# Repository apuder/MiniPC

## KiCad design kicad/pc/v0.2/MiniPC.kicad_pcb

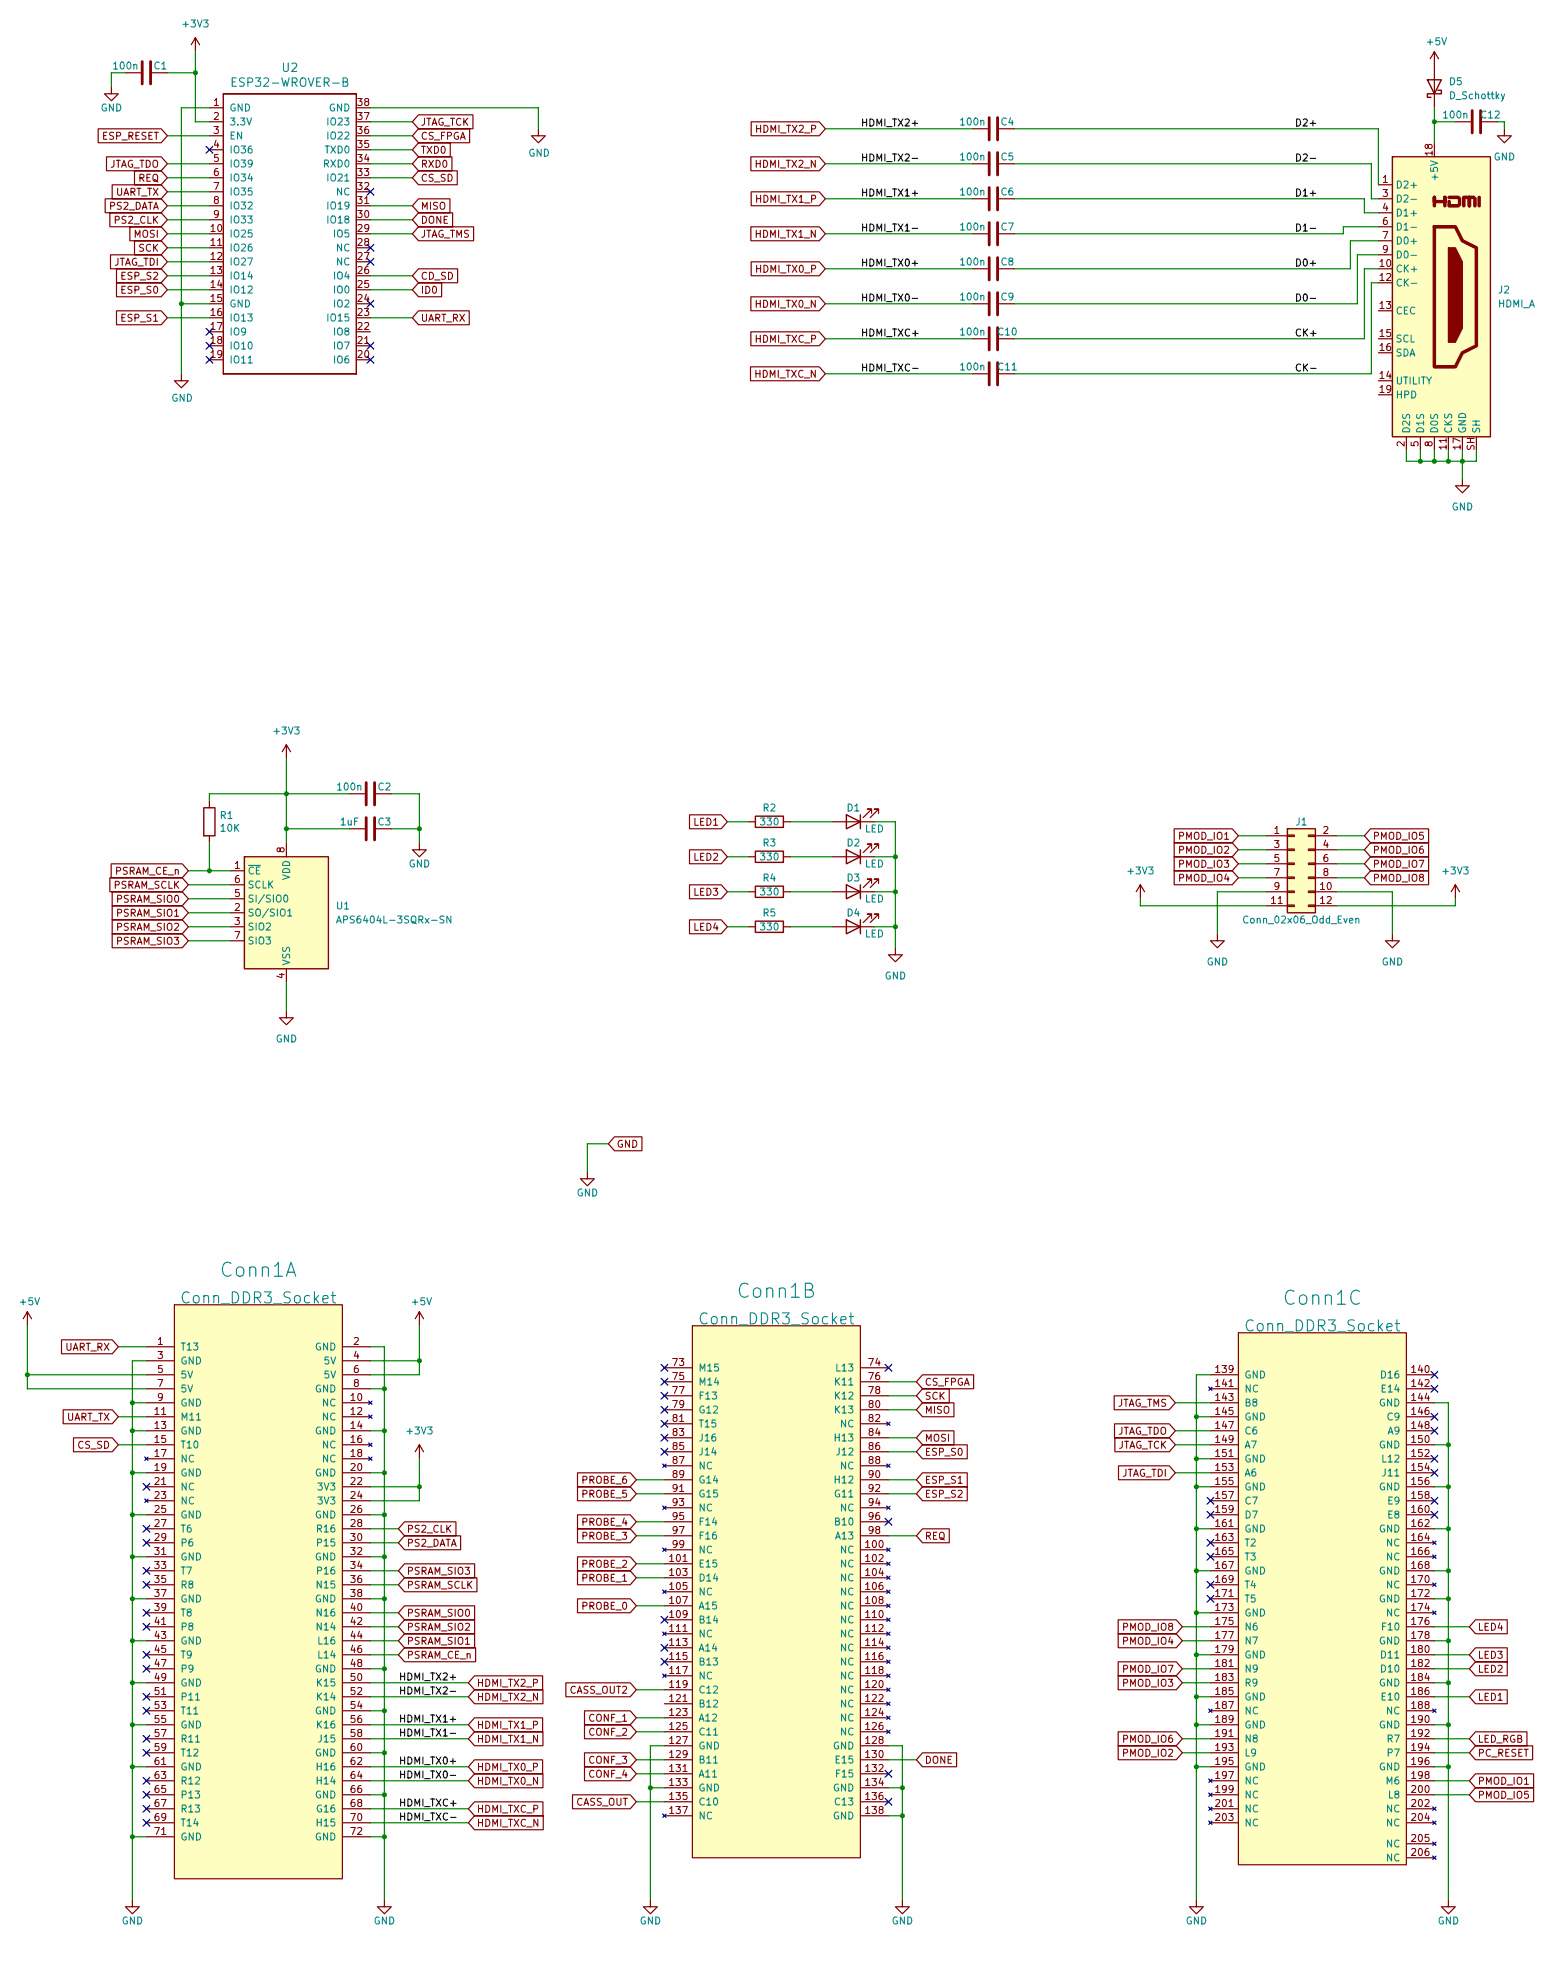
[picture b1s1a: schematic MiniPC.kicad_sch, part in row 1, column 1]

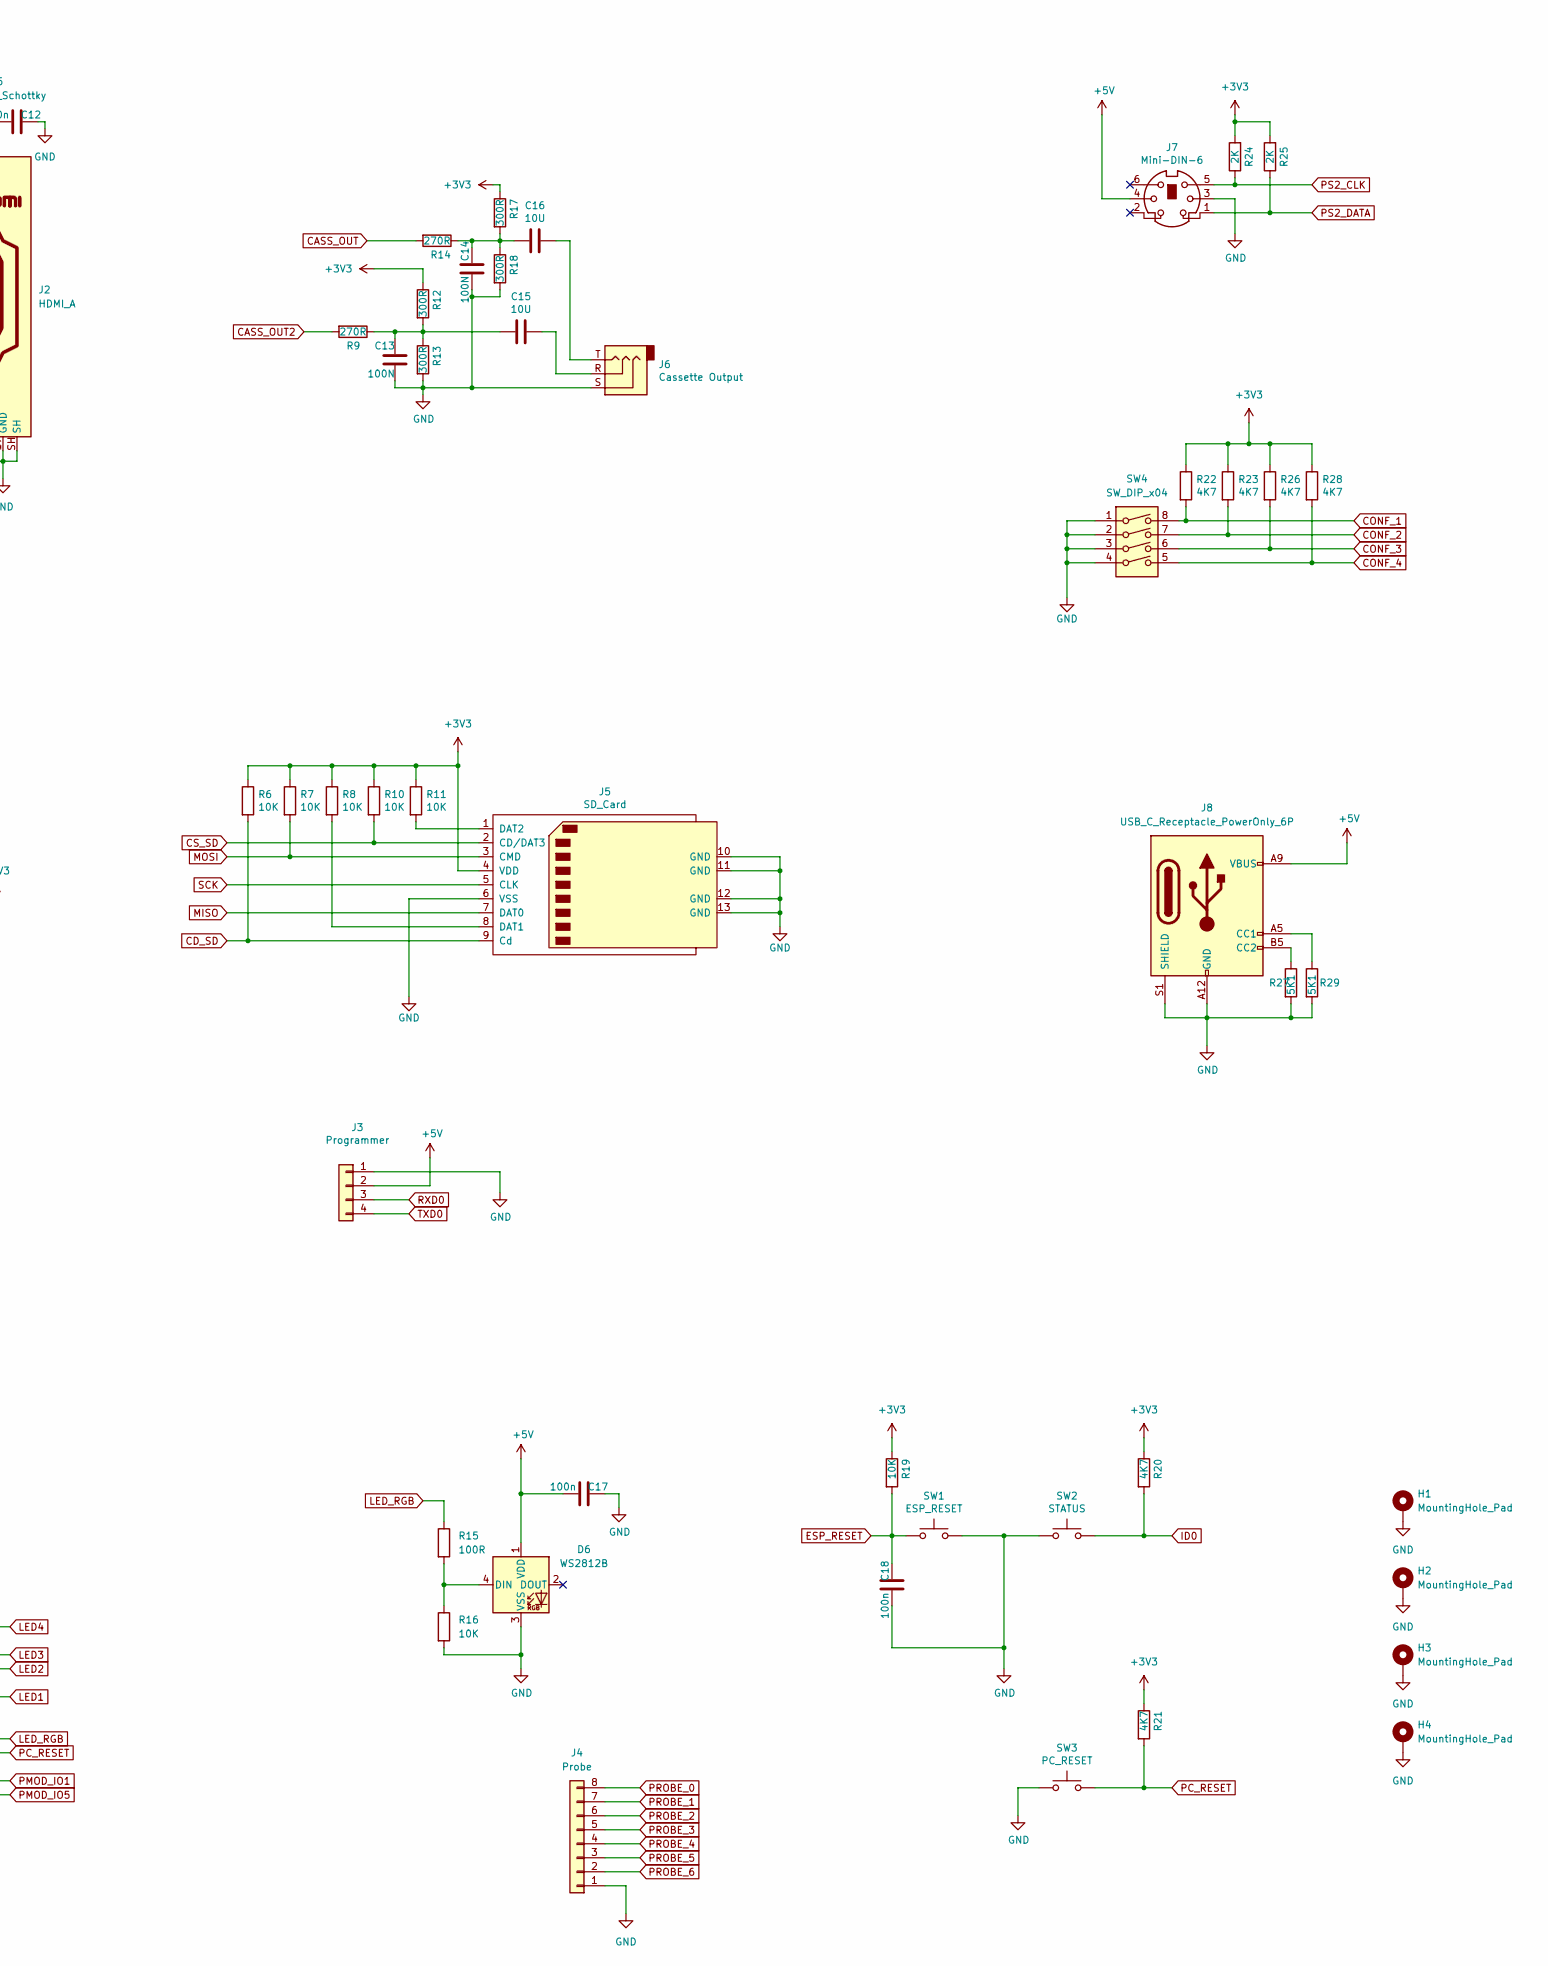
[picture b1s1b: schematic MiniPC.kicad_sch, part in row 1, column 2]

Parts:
C1, C2, C4, C5, C6, C7, C8, C9, C10, C11, C12, C17, C18: 100n; C_0805_2012Metric_Pad1.18x1.45mm_HandSolder
C3: 1uF; C_0805_2012Metric_Pad1.18x1.45mm_HandSolder
C13, C14: 100N; C_0805_2012Metric_Pad1.18x1.45mm_HandSolder
C15, C16: 10U; C_1206_3216Metric_Pad1.33x1.80mm_HandSolder
Conn1: Conn_DDR3_Socket; DDR3_socket; LCSC C306045
D1: LED; LED_0805_2012Metric_Pad1.15x1.40mm_HandSolder; LCSC C84256
D2, D3, D4: LED; LED_0805_2012Metric_Pad1.15x1.40mm_HandSolder
D5: D_Schottky; D_SOD-323; LCSC C1884554
D6: WS2812B; LED_WS2812B_PLCC4_5.0x5.0mm_P3.2mm; LCSC C2761795
H1, H2, H3, H4: MountingHole_Pad; MountingHole_3mm_Pad_Via
J1: Conn_02x06_Odd_Even; PinSocket_2x06_P2.54mm_Vertical; LCSC C358728
J2: HDMI_A; HDMI_A_Molex_208658-1001_Horizontal; LCSC C5184845
J3: Programmer; PinHeader_1x04_P2.54mm_Vertical; LCSC C2691448
J4: Probe; PinHeader_1x08_P2.54mm_Vertical
J5: SD_Card; TFP09-2-12B; LCSC C91145
J6: Cassette Output; Jack_3.5mm_CUI_SJ1-3535NG_Horizontal_CircularHoles; LCSC C2884945
J7: Mini-DIN-6; minidin_6_ps2_pcb_mount; LCSC C77848
J8: USB_C_Receptacle_PowerOnly_6P; USB_C_Receptacle_GCT_USB4125-xx-x_6P_TopMnt_Horizontal; LCSC C168701
R1, R6, R7, R8, R10, R11, R16, R19: 10K; R_0805_2012Metric_Pad1.20x1.40mm_HandSolder
R2, R3, R4, R5: 330; R_0805_2012Metric_Pad1.20x1.40mm_HandSolder
R9, R14: 270R; R_0805_2012Metric_Pad1.20x1.40mm_HandSolder
R12, R13, R17, R18: 300R; R_0805_2012Metric_Pad1.20x1.40mm_HandSolder
R15: 100R; R_0805_2012Metric_Pad1.20x1.40mm_HandSolder
R20, R21, R22, R23, R26, R28: 4K7; R_0805_2012Metric_Pad1.20x1.40mm_HandSolder
R24, R25: 2K; R_0805_2012Metric_Pad1.20x1.40mm_HandSolder
R27, R29: 5K1; R_0805_2012Metric_Pad1.20x1.40mm_HandSolder
SW1: ESP_RESET; SW_Push_1P1T_NO_E-Switch_TL3301NxxxxxG; LCSC C255812
SW2: STATUS; SW_Push_1P1T_NO_E-Switch_TL3301NxxxxxG; LCSC C255812
SW3: PC_RESET; SW_Push_1P1T_NO_E-Switch_TL3301NxxxxxG; LCSC C255812
SW4: SW_DIP_x04; SW_DIP_SPSTx04_Slide_6.7x11.72mm_W8.61mm_P2.54mm_LowProfile; LCSC C2842911
U1: APS6404L-3SQRx-SN; SOIC-8_3.9x4.9mm_P1.27mm; LCSC C5333729
U2: ESP32-WROVER-B; ESP32-WROVER; LCSC C529589

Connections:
+3V3: C1.2, C2.1, C3.1, Conn1.22 (3V3), Conn1.24 (3V3), J1.11, J1.12, J5.4 (VDD), R1.1, R6.1, R7.1, R8.1, R10.1, R11.1, R12.1, R17.1, R19.1, R20.1, R21.1, R22.1, R23.1, R24.2, R25.2, R26.1, R28.1, U1.8 (VDD), U2.2 (3.3V)
+5V: C17.1, Conn1.4 (5V), Conn1.5 (5V), Conn1.6 (5V), Conn1.7 (5V), D5.2 (A), D6.1 (VDD), J3.2, J7.4, J8.A9 (VBUS), J8.B9 (VBUS)
/CK+: C10.2, J2.10 (CK+)
/CK-: C11.2, J2.12 (CK-)
/D0+: C8.2, J2.7 (D0+)
/D0-: C9.2, J2.9 (D0-)
/D1+: C6.2, J2.4 (D1+)
/D1-: C7.2, J2.6 (D1-)
/D2+: C4.2, J2.1 (D2+)
/D2-: C5.2, J2.3 (D2-)
CASS_OUT: Conn1.135 (C10), R14.2
CASS_OUT2: Conn1.119 (C12), R9.2
CD_SD: J5.9 (Cd), R6.2, U2.26 (IO4)
CONF_1: Conn1.123 (A12), R22.2, SW4.8
CONF_2: Conn1.125 (C11), R23.2, SW4.7
CONF_3: Conn1.129 (B11), R26.2, SW4.6
CONF_4: Conn1.131 (A11), R28.2, SW4.5
CS_FPGA: Conn1.76 (K11), U2.36 (IO22)
CS_SD: Conn1.15 (T10), J5.2 (CD/DAT3), R10.2, U2.33 (IO21)
DONE: Conn1.130 (E15), U2.30 (IO18)
ESP_RESET: C18.2, R19.2, SW1.1, U2.3 (EN)
ESP_S0: Conn1.86 (J12), U2.14 (IO12)
ESP_S1: Conn1.90 (H12), U2.16 (IO13)
ESP_S2: Conn1.92 (G11), U2.13 (IO14)
GND: C1.1, C2.2, C3.2, C12.2, C13.2, C14.2, C17.2, C18.1, Conn1.2 (GND), Conn1.3 (GND), Conn1.8 (GND), Conn1.9 (GND), Conn1.13 (GND), Conn1.14 (GND), Conn1.19 (GND), Conn1.20 (GND), Conn1.25 (GND), Conn1.26 (GND), Conn1.31 (GND), Conn1.32 (GND), Conn1.37 (GND), Conn1.38 (GND), Conn1.43 (GND), Conn1.48 (GND), Conn1.49 (GND), Conn1.54 (GND), Conn1.55 (GND), Conn1.60 (GND), Conn1.61 (GND), Conn1.66 (GND), Conn1.71 (GND), Conn1.72 (GND), Conn1.127 (GND), Conn1.128 (GND), Conn1.133 (GND), Conn1.134 (GND), Conn1.138 (GND), Conn1.139 (GND), Conn1.144 (GND), Conn1.145 (GND), Conn1.150 (GND), Conn1.151 (GND), Conn1.155 (GND), Conn1.156 (GND), Conn1.161 (GND), Conn1.162 (GND), Conn1.167 (GND), Conn1.168 (GND), Conn1.172 (GND), Conn1.173 (GND), Conn1.178 (GND), Conn1.179 (GND), Conn1.184 (GND), Conn1.185 (GND), Conn1.189 (GND), Conn1.190 (GND), Conn1.195 (GND), Conn1.196 (GND), D1.1 (K), D2.1 (K), D3.1 (K), D4.1 (K), D6.3 (VSS), H1.1, H2.1, H3.1, H4.1, J1.9, J1.10, J2.2 (D2S), J2.5 (D1S), J2.8 (D0S), J2.11 (CKS), J2.17 (GND), J2.SH, J3.1, J4.1, J5.6 (VSS), J5.10 (GND), J5.11 (GND), J5.12 (GND), J5.13 (GND), J6.S, J7.3, J8.A12 (GND), J8.B12 (GND), J8.S1 (SHIELD), R13.2, R16.2, R18.2, R27.2, R29.2, SW1.2, SW2.1, SW3.1, SW4.1, SW4.2, SW4.3, SW4.4, U1.4 (VSS), U2.1 (GND), U2.15 (GND), U2.38 (GND)
HDMI_TX0_N: C9.1, Conn1.64 (H14)
HDMI_TX0_P: C8.1, Conn1.62 (H16)
HDMI_TX1_N: C7.1, Conn1.58 (J15)
HDMI_TX1_P: C6.1, Conn1.56 (K16)
HDMI_TX2_N: C5.1, Conn1.52 (K14)
HDMI_TX2_P: C4.1, Conn1.50 (K15)
HDMI_TXC_N: C11.1, Conn1.70 (H15)
HDMI_TXC_P: C10.1, Conn1.68 (G16)
ID0: R20.2, SW2.2, U2.25 (IO0)
JTAG_TCK: Conn1.149 (A7), U2.37 (IO23)
JTAG_TDI: Conn1.153 (A6), U2.12 (IO27)
JTAG_TDO: Conn1.147 (C6), U2.5 (IO39)
JTAG_TMS: Conn1.143 (B8), U2.29 (IO5)
LED1: Conn1.186 (E10), R2.1
LED2: Conn1.182 (D10), R3.1
LED3: Conn1.180 (D11), R4.1
LED4: Conn1.176 (F10), R5.1
LED_RGB: Conn1.192 (R7), R15.1
MISO: Conn1.80 (K13), J5.7 (DAT0), U2.31 (IO19)
MOSI: Conn1.84 (H13), J5.3 (CMD), R7.2, U2.10 (IO25)
unnamed: C13.1, C15.2, R9.1, R12.2, R13.1
unnamed: C14.1, C16.2, R14.1, R17.2, R18.1
unnamed: C15.1, J6.R
unnamed: C16.1, J6.T
unnamed: D1.2 (A), R2.2
unnamed: D2.2 (A), R3.2
unnamed: D3.2 (A), R4.2
unnamed: D4.2 (A), R5.2
unnamed: C12.1, D5.1 (K), J2.18 (+5V)
unnamed: D6.4 (DIN), R15.2, R16.1
unnamed: J5.8 (DAT1), R8.2
unnamed: J5.1 (DAT2), R11.2
unnamed: J8.A5 (CC1), R29.1
unnamed: J8.B5 (CC2), R27.1
PC_RESET: Conn1.194 (P7), R21.2, SW3.2
PMOD_IO1: Conn1.198 (M6), J1.1
PMOD_IO2: Conn1.193 (L9), J1.3
PMOD_IO3: Conn1.183 (R9), J1.5
PMOD_IO4: Conn1.177 (N7), J1.7
PMOD_IO5: Conn1.200 (L8), J1.2
PMOD_IO6: Conn1.191 (N8), J1.4
PMOD_IO7: Conn1.181 (N9), J1.6
PMOD_IO8: Conn1.175 (N6), J1.8
PROBE_0: Conn1.107 (A15), J4.8
PROBE_1: Conn1.103 (D14), J4.7
PROBE_2: Conn1.101 (E15), J4.6
PROBE_3: Conn1.97 (F16), J4.5
PROBE_4: Conn1.95 (F14), J4.4
PROBE_5: Conn1.91 (G15), J4.3
PROBE_6: Conn1.89 (G14), J4.2
PS2_CLK: Conn1.28 (R16), J7.5, R24.1, U2.9 (IO33)
PS2_DATA: Conn1.30 (P15), J7.1, R25.1, U2.8 (IO32)
PSRAM_CE_n: Conn1.46 (L14), R1.2, U1.1 (~CE)
PSRAM_SCLK: Conn1.36 (N15), U1.6 (SCLK)
PSRAM_SIO0: Conn1.40 (N16), U1.5 (SI/SIO0)
PSRAM_SIO1: Conn1.44 (L16), U1.2 (SO/SIO1)
PSRAM_SIO2: Conn1.42 (N14), U1.3 (SIO2)
PSRAM_SIO3: Conn1.34 (P16), U1.7 (SIO3)
REQ: Conn1.98 (A13), U2.6 (IO34)
RXD0: J3.3, U2.34 (RXD0)
SCK: Conn1.78 (K12), J5.5 (CLK), U2.11 (IO26)
TXD0: J3.4, U2.35 (TXD0)
UART_RX: Conn1.1 (T13), U2.23 (IO15)
UART_TX: Conn1.11 (M11), U2.7 (IO35)

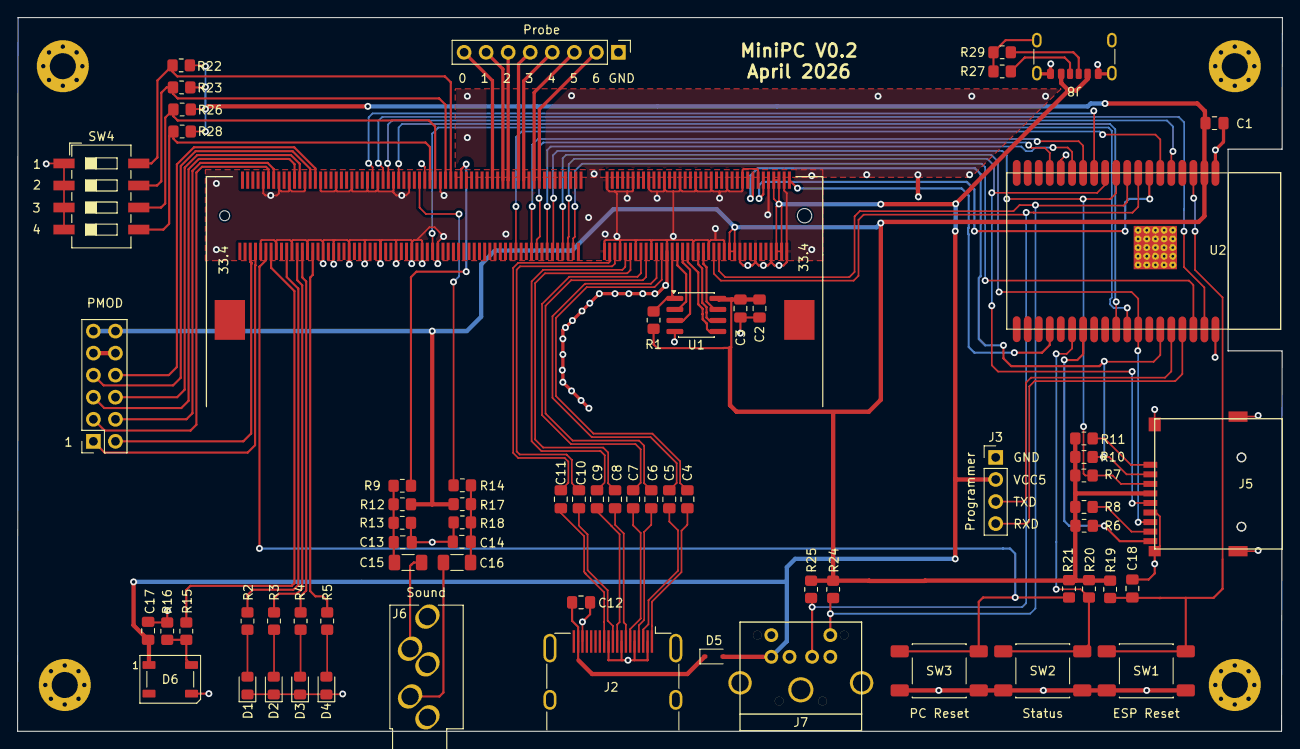
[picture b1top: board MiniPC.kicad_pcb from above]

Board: 2 copper layers, 145.7 x 82.2 mm, 72 parts (0 on the bottom side), 89 nets.

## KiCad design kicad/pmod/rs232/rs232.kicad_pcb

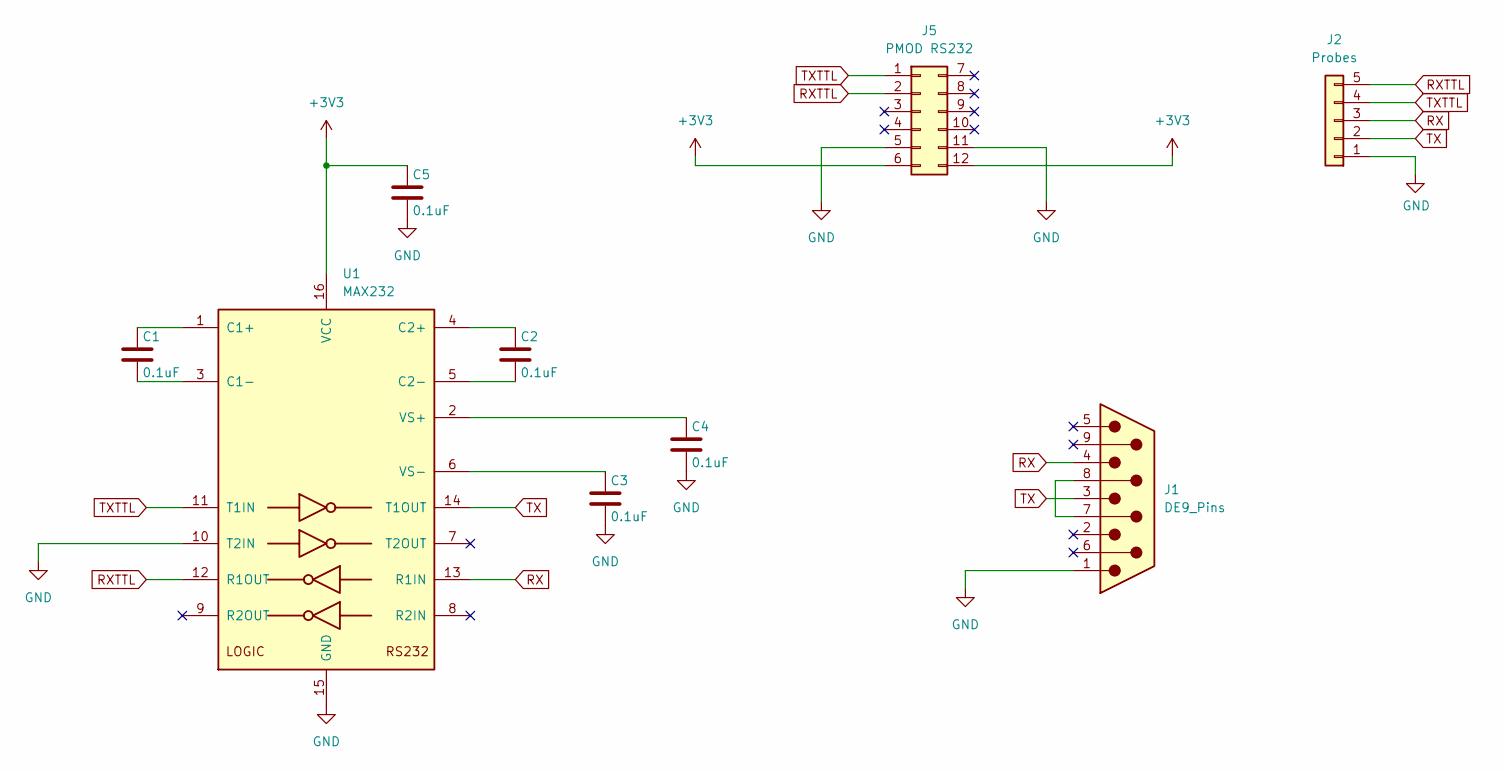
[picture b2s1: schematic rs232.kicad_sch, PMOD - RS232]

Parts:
C1, C2, C3, C4, C5: 0.1uF; C_0805_2012Metric_Pad1.18x1.45mm_HandSolder; LCSC C49678
J1: DE9_Pins; DSUB-9_Socket_Horizontal_P2.77x2.84mm_EdgePinOffset7.70mm_H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
J2: Probes; PinHeader_1x05_P2.54mm_Vertical
J5: PMOD RS232; PinSocket_2x06_Top_Bottom_P2.54mm_Vertical; LCSC C358728
U1: MAX232; TSSOP-16_4.4x5mm_P0.65mm; LCSC C406863

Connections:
+3V3: C5.1, J5.6, J5.12, U1.16 (VCC)
GND: C3.2, C4.2, C5.2, J1.1, J2.1, J5.5, J5.11, U1.10 (T2IN), U1.15 (GND)
unnamed: J1.7, J1.8
unnamed: C1.1, U1.1 (C1+)
unnamed: C1.2, U1.3 (C1-)
unnamed: C2.1, U1.4 (C2+)
unnamed: C2.2, U1.5 (C2-)
unnamed: C4.1, U1.2 (VS+)
unnamed: C3.1, U1.6 (VS-)
RX: J1.4, J2.3, U1.13 (R1IN)
RXTTL: J2.5, J5.2, U1.12 (R1OUT)
TX: J1.3, J2.2, U1.14 (T1OUT)
TXTTL: J2.4, J5.1, U1.11 (T1IN)

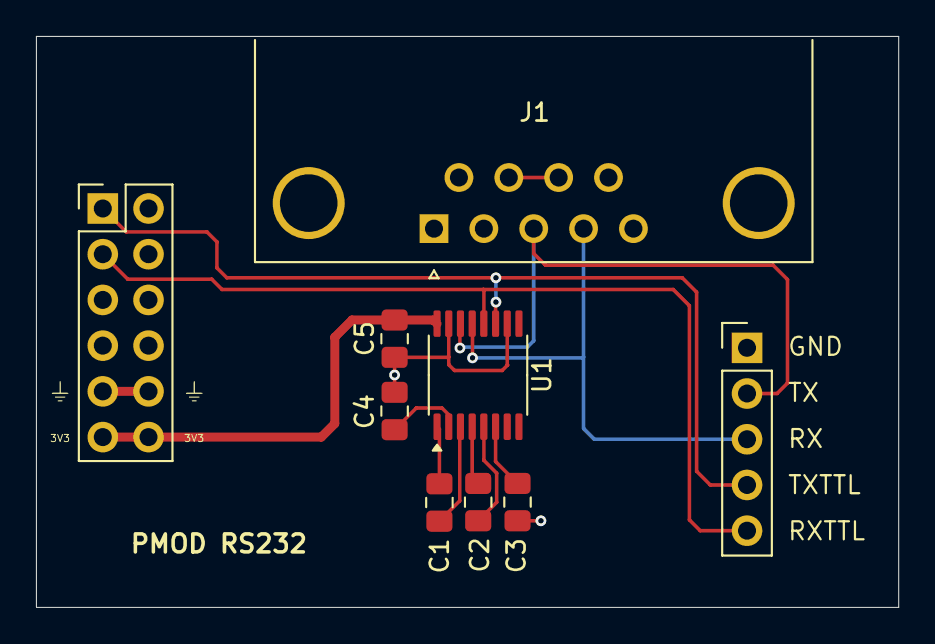
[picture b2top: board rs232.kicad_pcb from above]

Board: 2 copper layers, 47.9 x 31.7 mm, 9 parts (0 on the bottom side), 13 nets.

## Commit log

2026-02-27 v0.1 of KiCad schematics and PCB
2026-03-03 RISC core. PSRAM controller
2026-03-04 Add display BRAM connected to RISC core
2026-03-05 Integrate PTRS M4 display from TRS-IO project
2026-03-05 Move MiniPC KiCad files to sub-directory
2026-03-08 Version 0.2 of MiniPC PCB
2026-03-08 RS 232 PMOD PCB
2026-03-12 Add SPI client implementation
2026-03-18 SPI - FPGA
2026-03-19 Moved mini-pc to v0.1 directory
2026-03-19 Add flash bridge (FPGA)
2026-03-19 Add initial ESP firmware (Programmer-20K)
2026-03-22 First version of loading kernel.bin (not working)
2026-03-23 Almost working SPI (except first byte of MISO)
2026-03-23 Working SPI implementation
2026-03-23 First working boot from PSRAM
2026-03-25 Import of x86 version of TOS
2026-03-26 TOS Hello World (via UART)
2026-03-28 Enable 80x24 text mode
2026-03-28 Drop SPI SCK to 5 MHz. Various timing fixes
2026-03-28 More robust startup.s. Handle global variable initialization
2026-03-28 Integrate TOS simple window system
2026-03-29 Ported TOS test harness
2026-03-29 Fix for test_window_5
2026-03-31 Working create_process() and resign()
2026-03-31 Fix for 16-bit sized PSRAM access
2026-03-31 Added IPC tests
2026-04-03 Working preemptive multi-tasking
2026-04-03 Fix for corrupt context
2026-04-03 Ported window manager
2026-04-07 Make sbrk() return word-aligned addresses
2026-04-09 Version 0.2 (April) of MiniPC PCB
2026-04-09 SDcard upload added.
2026-04-10 FAT FS LFS support enabled.
2026-04-10 Enable RISC small data segment
2026-04-10 Fix corrupted t0 in context switch. Added shell and pong
2026-04-14 Fix for context corruption. Added UART IRQ
2026-04-15 WM performance improvements
2026-04-17 Added UART2
2026-04-18 Fix for PSRAM soft reset
2026-04-24 Update PONG paddle
2026-04-24 Fix CDC issue in UART RX path
2026-04-24 Support for PS/2 keyboard
